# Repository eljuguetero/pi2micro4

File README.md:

Raspberry-Pi to Microduino bridge board.

Top layer
=========
![Front](
https://github.com/eljuguetero/pi2micro4/blob/master/Gerbers/front.png)

Bottom layer
============
![Back](
https://github.com/eljuguetero/pi2micro4/blob/master/Gerbers/back.png)

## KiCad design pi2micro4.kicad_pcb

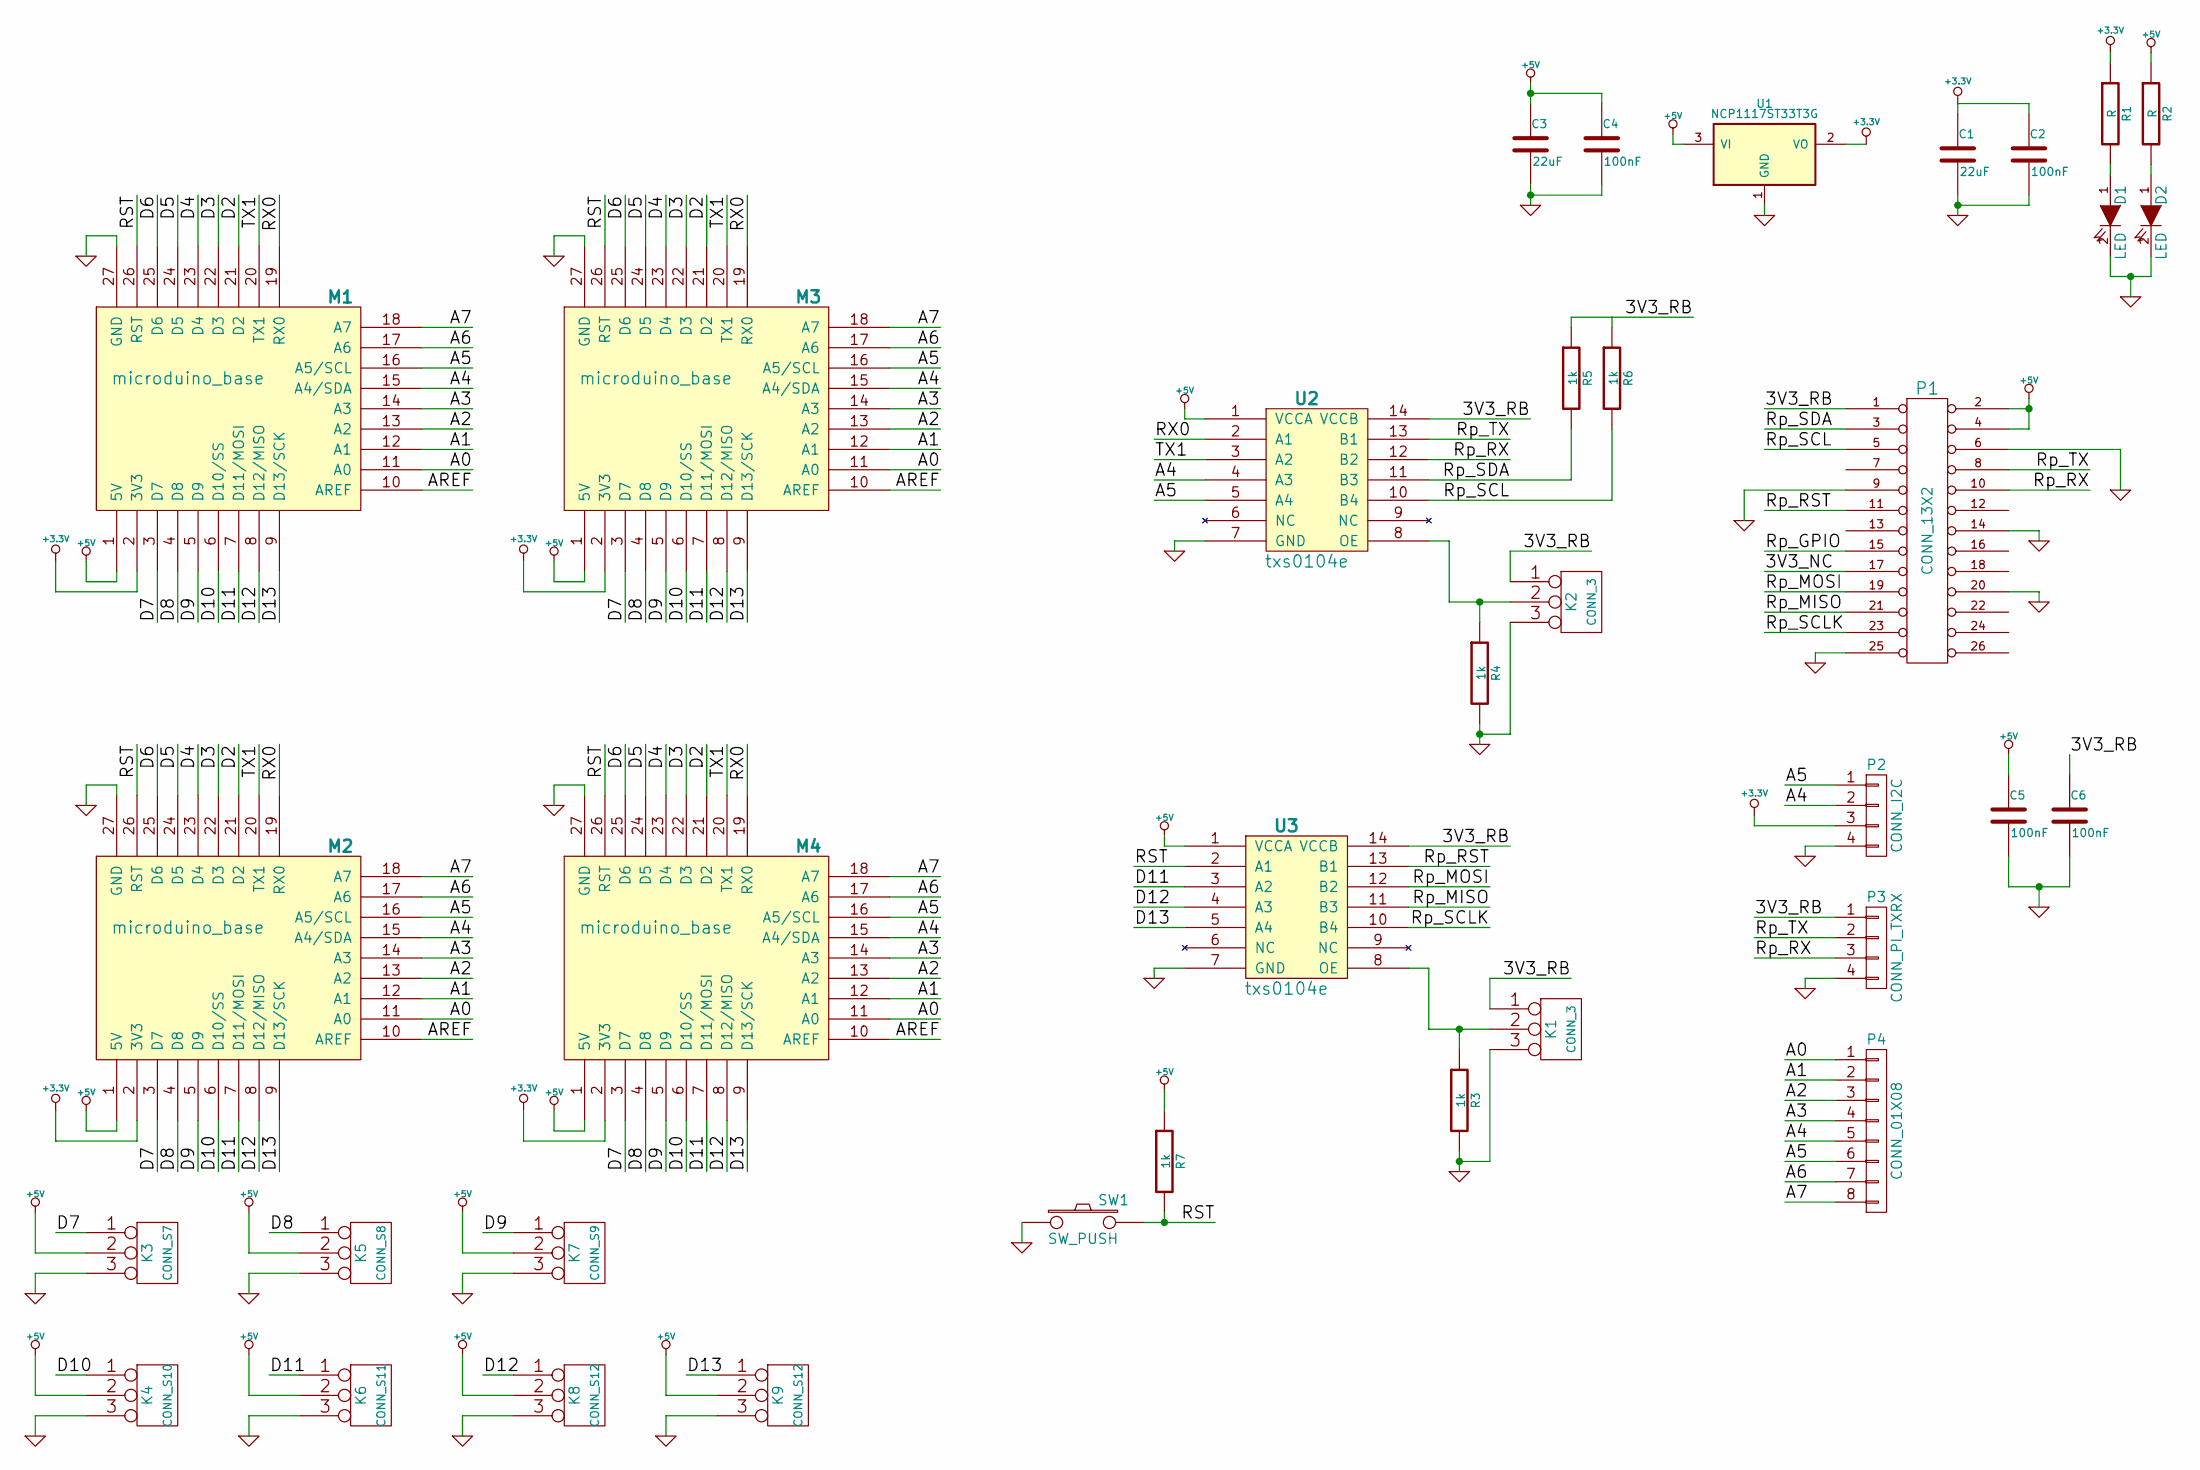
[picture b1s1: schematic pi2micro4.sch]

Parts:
C1, C3: 22uF; SMD-1206
C2, C4, C5, C6: 100nF; SMD-0603
D1, D2: LED; SMD-0603
K1, K2: CONN_3; SIL-3
K3: CONN_S7; SIL-3
K4: CONN_S10; SIL-3
K5: CONN_S8; SIL-3
K6: CONN_S11; SIL-3
K7: CONN_S9; SIL-3
K8, K9: CONN_S12; SIL-3
M1, M2, M3, M4: microduino_base
P1: CONN_13X2; Pin_Header_Straight_2x13
P2: CONN_I2C; SIL-4
P3: CONN_PI_TXRX; SIL-4
P4: CONN_01X08
R1, R2: R; SMD-0603
R3, R4, R5, R6, R7: 1k; SMD-0603
SW1: SW_PUSH; SW_PUSH_SMALL
U1: NCP1117ST33T3G; SOT-223
U2, U3: txs0104e; TSSOP-14

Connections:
+3.3V: C1.1, C2.1, M1.2 (3V3), M2.2 (3V3), M3.2 (3V3), M4.2 (3V3), P2.3, R1.1, U1.2 (VO)
+5V: C3.1, C4.1, C5.1, K3.2 (PM), K4.2 (PM), K5.2 (PM), K6.2 (PM), K7.2 (PM), K8.2 (PM), K9.2 (PM), M1.1 (5V), M2.1 (5V), M3.1 (5V), M4.1 (5V), P1.2, P1.4, R2.1, R7.1, U1.3 (VI), U2.1 (VCCA), U3.1 (VCCA)
/3V3_RB: C6.1, K1.1, K2.1, P1.1, P3.1, R5.1, U2.14 (VCCB), U3.14 (VCCB)
/A0: M1.11 (A0), M2.11 (A0), M3.11 (A0), M4.11 (A0), P4.1
/A1: M1.12 (A1), M2.12 (A1), M3.12 (A1), M4.12 (A1), P4.2
/A2: M1.13 (A2), M2.13 (A2), M3.13 (A2), M4.13 (A2), P4.3
/A3: M1.14 (A3), M2.14 (A3), M3.14 (A3), M4.14 (A3), P4.4
/A4: M1.15 (A4/SDA), M2.15 (A4/SDA), M3.15 (A4/SDA), M4.15 (A4/SDA), P2.2, P4.5, U2.4 (A3)
/A5: M1.16 (A5/SCL), M2.16 (A5/SCL), M3.16 (A5/SCL), M4.16 (A5/SCL), P2.1, P4.6, U2.5 (A4)
/A6: M1.17 (A6), M2.17 (A6), M3.17 (A6), M4.17 (A6), P4.7
/A7: M1.18 (A7), M2.18 (A7), M3.18 (A7), M4.18 (A7), P4.8
/AREF: M1.10 (AREF), M2.10 (AREF), M3.10 (AREF), M4.10 (AREF)
/D2: M1.21 (D2), M2.21 (D2), M3.21 (D2), M4.21 (D2)
/D3: M1.22 (D3), M2.22 (D3), M3.22 (D3), M4.22 (D3)
/D4: M1.23 (D4), M2.23 (D4), M3.23 (D4), M4.23 (D4)
/D5: M1.24 (D5), M2.24 (D5), M3.24 (D5), M4.24 (D5)
/D6: M1.25 (D6), M2.25 (D6), M3.25 (D6), M4.25 (D6)
/D7: K3.1, M1.3 (D7), M2.3 (D7), M3.3 (D7), M4.3 (D7)
/D8: K5.1, M1.4 (D8), M2.4 (D8), M3.4 (D8), M4.4 (D8)
/D9: K7.1, M1.5 (D9), M2.5 (D9), M3.5 (D9), M4.5 (D9)
/D10: K4.1, M1.6 (D10/SS), M2.6 (D10/SS), M3.6 (D10/SS), M4.6 (D10/SS)
/D11: K6.1, M1.7 (D11/MOSI), M2.7 (D11/MOSI), M3.7 (D11/MOSI), M4.7 (D11/MOSI), U3.3 (A2)
/D12: K8.1, M1.8 (D12/MISO), M2.8 (D12/MISO), M3.8 (D12/MISO), M4.8 (D12/MISO), U3.4 (A3)
/D13: K9.1, M1.9 (D13/SCK), M2.9 (D13/SCK), M3.9 (D13/SCK), M4.9 (D13/SCK), U3.5 (A4); also elsewhere on the board
/RST: M1.26 (RST), M2.26 (RST), M3.26 (RST), M4.26 (RST), R7.2, SW1.2, U3.2 (A1)
/RX0: M1.19 (RX0), M2.19 (RX0), M3.19 (RX0), M4.19 (RX0), U2.2 (A1)
/Rp_MISO: P1.21, U3.11 (B3)
/Rp_MOSI: P1.19, U3.12 (B2)
/Rp_RST: P1.11, U3.13 (B1)
/Rp_RX: P1.10, P3.3, U2.12 (B2)
/Rp_SCL: P1.5, R6.2, U2.10 (B4)
/Rp_SCLK: P1.23, U3.10 (B4)
/Rp_SDA: P1.3, R5.2, U2.11 (B3)
/Rp_TX: P1.8, P3.2, U2.13 (B1)
/TX1: M1.20 (TX1), M2.20 (TX1), M3.20 (TX1), M4.20 (TX1), U2.3 (A2)
GND: C1.2, C2.2, C3.2, C4.2, C5.2, C6.2, D1.2 (K), D2.2 (K), K1.3, K2.3, K3.3, K4.3, K5.3, K6.3, K7.3, K8.3, K9.3, M1.27 (GND), M2.27 (GND), M3.27 (GND), M4.27 (GND), P1.6, P1.9, P1.14, P1.20, P1.25 (P24), P2.4, P3.4, R3.2, R4.2, SW1.1, U1.1 (GND), U2.7 (GND), U3.7 (GND); also elsewhere on the board
unnamed: D1.1 (A), R1.2
unnamed: D2.1 (A), R2.2
unnamed: K1.2 (PM), R3.1, U3.8 (OE)
unnamed: K2.2 (PM), R4.1, U2.8 (OE)

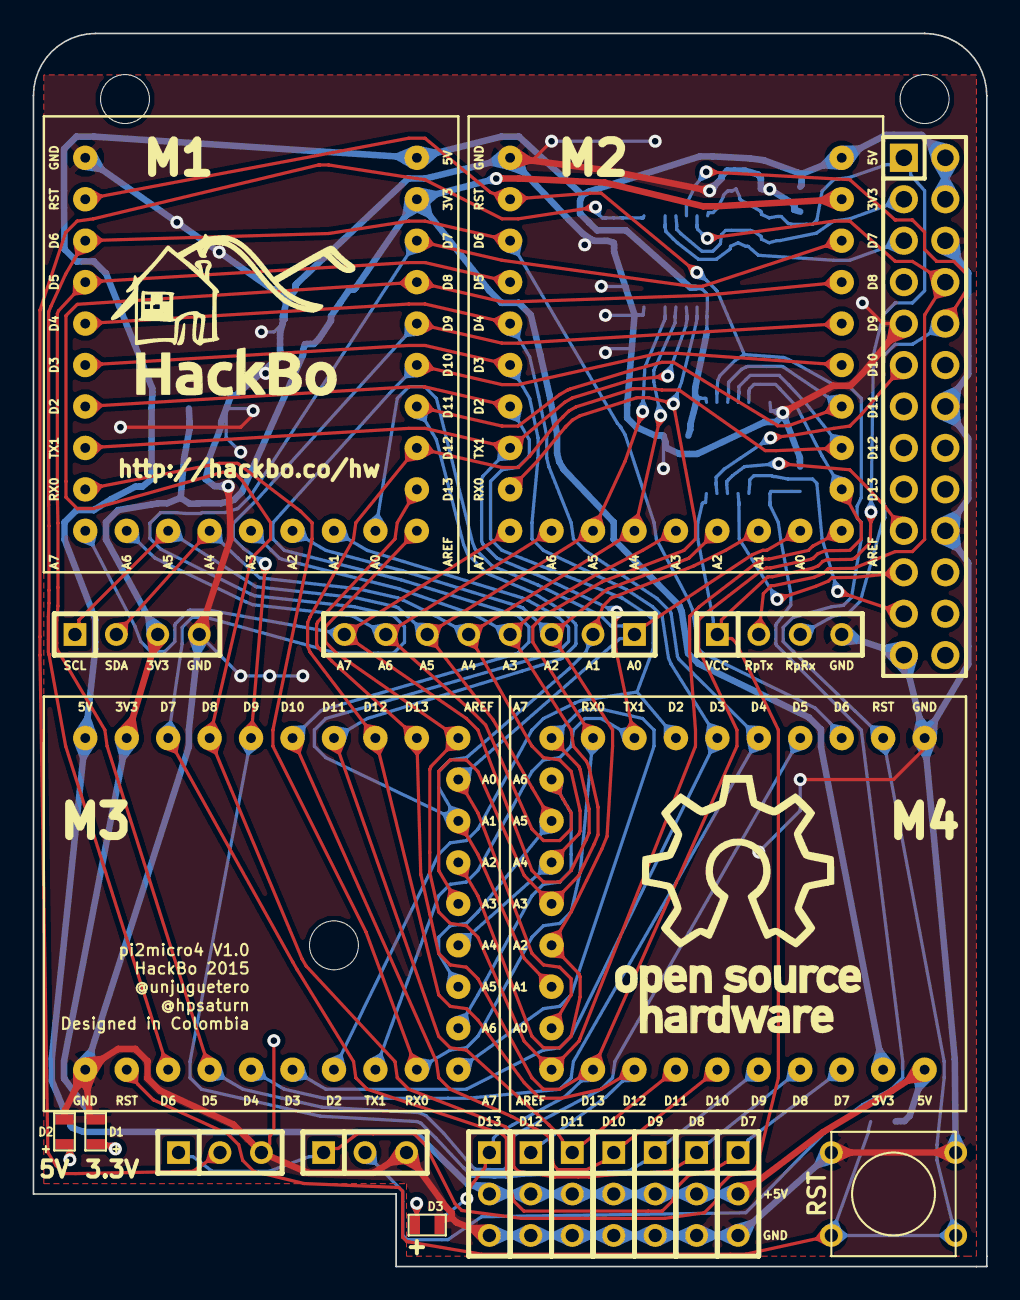
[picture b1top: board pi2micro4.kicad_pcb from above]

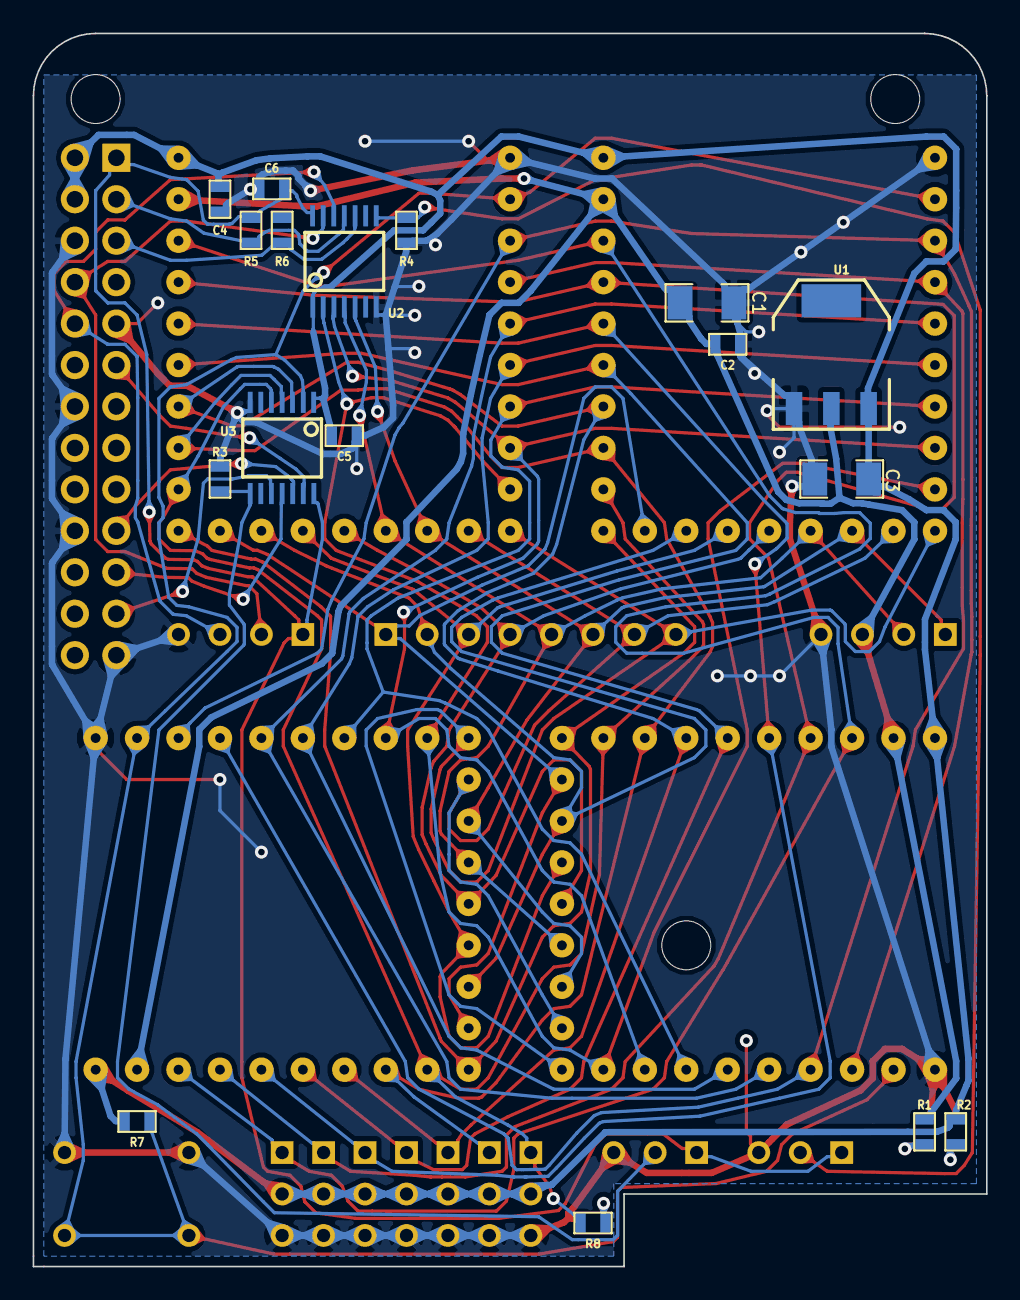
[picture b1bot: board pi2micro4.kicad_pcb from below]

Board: 2 copper layers, 58.4 x 75.6 mm, 43 parts (17 on the bottom side), 41 nets.

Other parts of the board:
D3: LED; SMD-0603
G1: LOGO; hackbo
G2: LOGO; oshw
MH1, MH2, MH3: MountingHole_4mm_RevA_Date21Jun2010; MountingHole_3mm
R8: R; SMD-0603

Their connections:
/D13: R8.1; also elsewhere on the board
GND: D3.2; also elsewhere on the board
unnamed: D3.1, R8.2

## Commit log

2014-08-29 first version
2014-09-06 nuevo buffer
2014-09-07 corregido el footprint del microduino
2014-09-07 logo de hackbo para kicad
2014-09-07 logo de openhardware
2014-09-07 labels
2014-09-07 gerber files
2014-09-07 previsualizaciones
2014-09-09 dimmensions from Pi model B
2014-09-09 add usb dimmension
2014-09-13 guias
2014-09-13 6 conectores para servos
2014-09-13 mejorando planos de tierra
2014-09-16 conectores de entrada analoga y uart a las raspberry pi
2014-09-17 D13 led
2014-10-21 LICENSE
2014-10-21 imagenes
2014-10-21 README.md updated
2015-06-10 mounting holes replacement
